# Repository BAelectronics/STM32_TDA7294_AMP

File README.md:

# Kapcsolódó videók / Related videos
[Part 1 (showing)](https://youtu.be/A-13wsFyjP8)
The language of the video is Hungarian, but English subtitles are available.

[Part 2 (HW & SW részletek)](https://youtu.be/WkM5X-X5rjU)

# STM32 vezérelt TDA7294 erősítő
A videóban bemutatott és a projekthez tartozó fájlok, rajzok, kódok stb.

A vezérlőpanel kapcsolása és nyákterve KiCad 5.1 programmal készült.
Az erősítőpanel és a táppanel Sprint Layout 5.0 programmal készült.
Az erősítőpanel kapcsolási rajza nem saját tervezés, ez képként megtalálható.

# STM32 Controlled TDA7294 Amplifier
Files, schematics, codes, etc. Everything what presented in the video and associated with the project.

The control board schematic and PCB designed with KiCad 5.1.
The amplifier board and power supply board designed with Sprint Layout 5.0.
The schematic of the amplifier board is not my own design, it can be found as picture.

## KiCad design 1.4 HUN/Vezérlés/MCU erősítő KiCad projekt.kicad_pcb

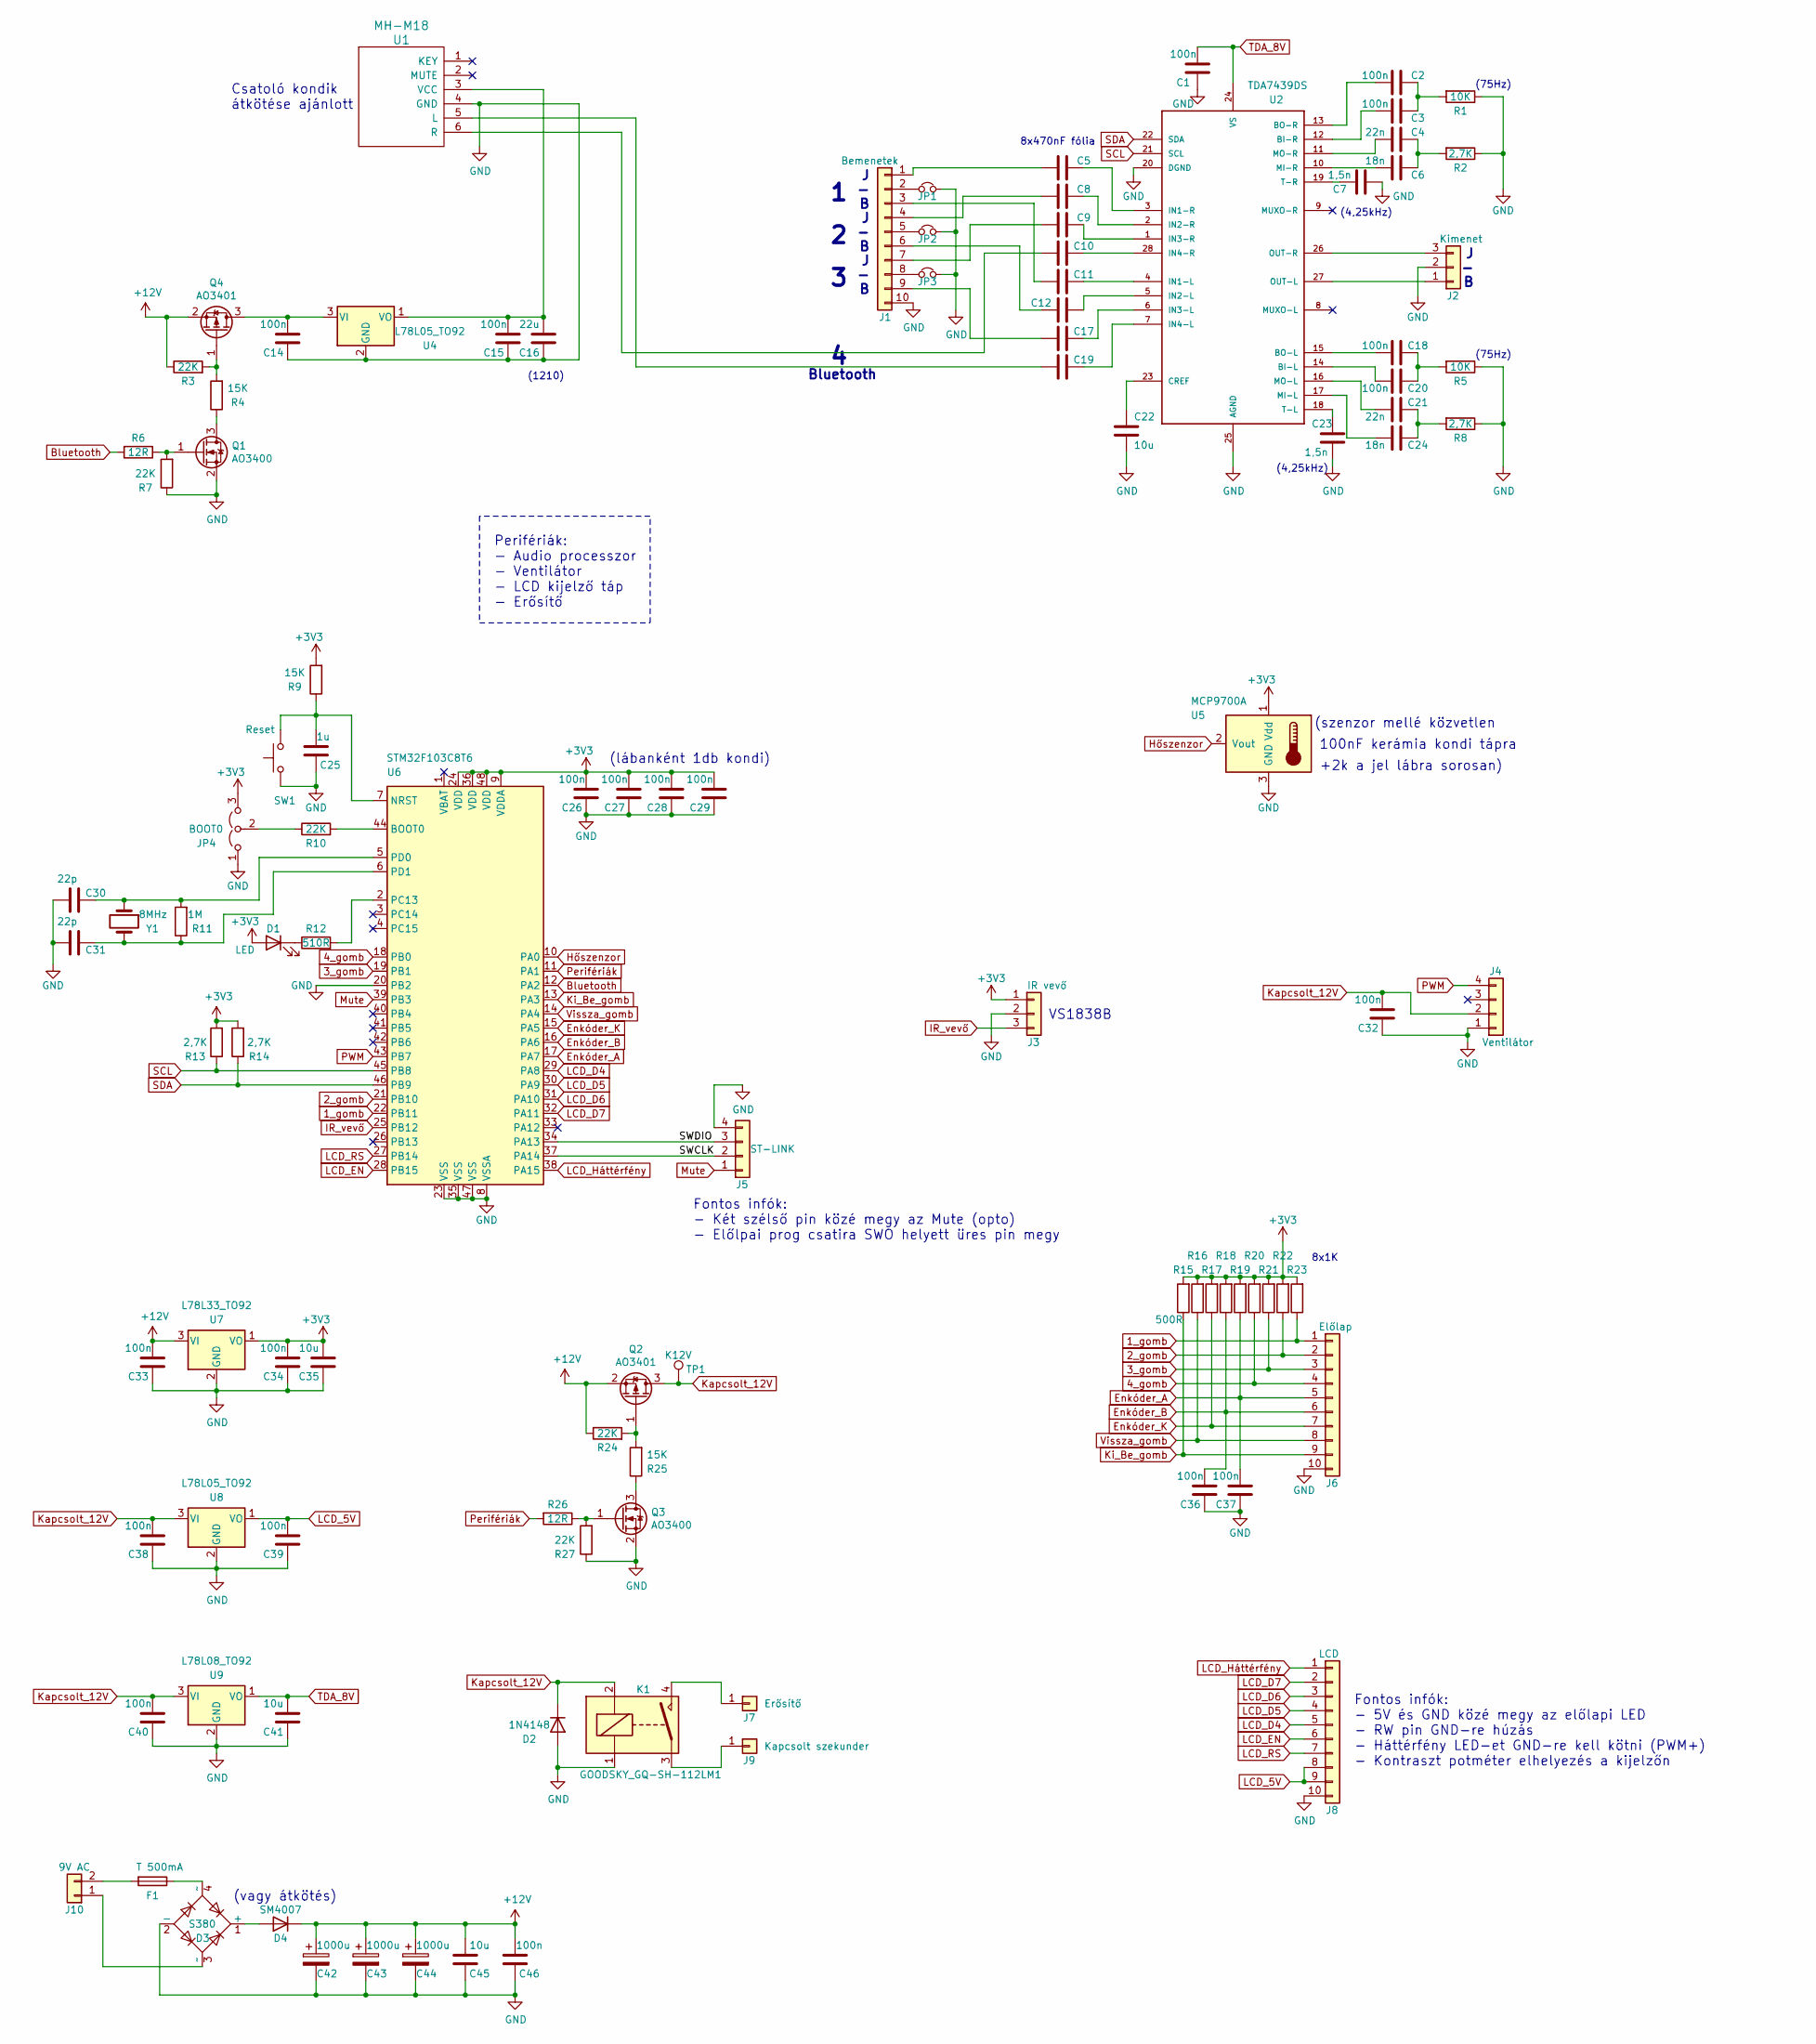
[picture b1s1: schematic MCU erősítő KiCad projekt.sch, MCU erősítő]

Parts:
C1, C14, C15, C26, C27, C28, C29, C32, C33, C34, C36, C37, C38, C39, C40, C46: 100n; C_0805_2012Metric
C2, C3, C18, C20: 100n; C_Rect_L7.0mm_W2.5mm_P5.00mm
C4, C21: 22n; C_Rect_L7.0mm_W2.5mm_P5.00mm
C5, C8, C9, C10, C11, C12, C17, C19: 470n; C_Rect_L7.2mm_W3.5mm_P5.00mm_FKS2_FKP2_MKS2_MKP2
C6, C24: 18n; C_Rect_L7.0mm_W2.5mm_P5.00mm
C7, C23: 1,5n; C_Rect_L7.0mm_W2.5mm_P5.00mm
C16: 22u; C_1210_3225Metric
C22, C35, C41, C45: 10u; C_1206_3216Metric
C25: 1u; C_0805_2012Metric
C30, C31: 22p; C_0805_2012Metric
C42, C43, C44: 1000u; CP_Radial_D8.0mm_P3.50mm
D1: LED; LED_0805_2012Metric
D2: 1N4148; D_DO-35_SOD27_P7.62mm_Horizontal
D3: S380; Diode_Bridge_TO-269AA
D4: SM4007; D_MELF
F1: T 500mA; Fuse_Littelfuse_372_D8.50mm
J1: Bemenetek; JST_PH_B10B-PH-K_1x10_P2.00mm_Vertical
J2: Kimenet; JST_PH_B3B-PH-K_1x03_P2.00mm_Vertical
J3: IR vevő; JST_PH_B3B-PH-K_1x03_P2.00mm_Vertical
J4: Ventilátor; Molex_KK-254_AE-6410-04A_1x04_P2.54mm_Vertical
J5: ST-LINK; JST_PH_B4B-PH-K_1x04_P2.00mm_Vertical
J6: Előlap; JST_PH_B10B-PH-K_1x10_P2.00mm_Vertical
J7: Erősítő; SolderWirePad_1x02_P5.08mm_Drill1.5mm_saru
J8: LCD; JST_PH_B10B-PH-K_1x10_P2.00mm_Vertical
J9: Kapcsolt szekunder; SolderWirePad_1x02_P5.08mm_Drill1.5mm_saru
J10: 9V AC; TerminalBlock_RND_205-00012_1x02_P5.00mm_Horizontal
JP1: Jumper_1_GND; SolderJumper-2_P1.3mm_Open_Pad1.0x1.5mm
JP2: Jumper_2_GND; SolderJumper-2_P1.3mm_Open_Pad1.0x1.5mm
JP3: Jumper_3_GND; SolderJumper-2_P1.3mm_Open_Pad1.0x1.5mm
JP4: BOOT0; PinHeader_1x03_P2.54mm_Vertical
K1: GOODSKY_GQ-SH-112LM1
Q1, Q3: AO3400; SOT-23
Q2, Q4: AO3401; SOT-23
R1, R5: 10K; R_0805_2012Metric
R2, R8, R13, R14: 2,7K; R_0805_2012Metric
R3, R7, R10, R24, R27: 22K; R_0805_2012Metric
R4, R9: 15K; R_0805_2012Metric
R6, R26: 12R; R_0805_2012Metric
R11: 1M; R_0805_2012Metric
R12: 510R; R_0805_2012Metric
R15: 500R; R_0805_2012Metric
R16, R17, R18, R19, R20, R21, R22, R23: 1K; R_0805_2012Metric
R25: 15K; R_1206_3216Metric
SW1: Reset; SW_SPST_FSMSM
TP1: K12V; TestPoint_Pad_D1.0mm
U1: MH-M18; MH-M18_Bluetooth_Audio
U2: TDA7439DS; SOIC-28W_7.5x17.9mm_P1.27mm
U4, U8: L78L05_TO92; TO-92_Inline_mod
U5: MCP9700A; JST_PH_B3B-PH-K_1x03_P2.00mm_Vertical
U6: STM32F103C8T6; LQFP-48_7x7mm_P0.5mm
U7: L78L33_TO92; TO-92_Inline_mod
U9: L78L08_TO92; TO-92_Inline_mod
Y1: 8MHz; Crystal_HC49-U_Vertical

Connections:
1_gomb: J6.1, R23.1, U6.22 (PB11)
2_gomb: J6.2, R22.1, U6.21 (PB10)
3_gomb: J6.3, R21.1, U6.19 (PB1)
4_gomb: J6.4, R20.1, U6.18 (PB0)
+3V3: C26.2, C27.2, C28.2, C29.2, C34.2, C35.2, D1.2 (A), J3.1, JP4.3 (B), R9.2, R13.2, R14.2, R15.2, R16.2, R17.2, R18.2, R19.2, R20.2, R21.2, R22.2, R23.2, U5.1 (Vdd), U6.9 (VDDA), U6.24 (VDD), U6.36 (VDD), U6.48 (VDD), U7.1 (VO)
+12V: C33.2, C42.1, C43.1, C44.1, C45.2, C46.2, D4.1 (K), Q2.2 (S), Q4.2 (S), R3.1, R24.1, U7.3 (VI)
/SWCLK: J5.2, U6.37 (PA14)
/SWDIO: J5.3, U6.34 (PA13)
Bluetooth: R6.2, U6.12 (PA2)
Enkóder_A: C37.2, J6.5, R19.1, U6.17 (PA7)
Enkóder_B: C36.2, J6.6, R18.1, U6.16 (PA6)
Enkóder_K: J6.7, R17.1, U6.15 (PA5)
GND: C1.1, C7.2, C14.1, C15.1, C16.1, C22.1, C23.1, C25.1, C26.1, C27.1, C28.1, C29.1, C30.1, C31.1, C32.1, C33.1, C34.1, C35.1, C36.1, C37.1, C38.1, C39.1, C40.1, C41.1, C42.2, C43.2, C44.2, C45.1, C46.1, D2.2 (A), D3.2 (-), J1.10, J2.2, J3.2, J4.1, J5.4, J6.10, J8.10, JP1.2, JP2.2, JP3.2, JP4.1 (A), K1.1, Q1.2 (S), Q3.2 (S), R1.1, R2.1, R5.1, R7.1, R8.1, R27.1, SW1.1, U1.4 (GND), U2.20 (DGND), U2.25 (AGND), U4.2 (GND), U5.3 (GND), U6.8 (VSSA), U6.20 (PB2), U6.23 (VSS), U6.35 (VSS), U6.47 (VSS), U7.2 (GND), U8.2 (GND), U9.2 (GND)
Hőszenzor: U5.2 (Vout), U6.10 (PA0)
IR_vevő: J3.3, U6.25 (PB12)
Kapcsolt_12V: C32.2, C38.2, C40.2, D2.1 (K), J4.2, K1.2, Q2.3 (D), TP1.1, U8.3 (VI), U9.3 (VI)
Ki_Be_gomb: J6.9, R15.1, U6.13 (PA3)
LCD_5V: C39.2, J8.8, J8.9, U8.1 (VO)
LCD_D4: J8.5, U6.29 (PA8)
LCD_D5: J8.4, U6.30 (PA9)
LCD_D6: J8.3, U6.31 (PA10)
LCD_D7: J8.2, U6.32 (PA11)
LCD_EN: J8.6, U6.28 (PB15)
LCD_Háttérfény: J8.1, U6.38 (PA15)
LCD_RS: J8.7, U6.27 (PB14)
Mute: J5.1, U6.39 (PB3)
unnamed: C2.1, C3.1, R1.2
unnamed: C2.2, U2.13 (BO-R)
unnamed: C3.2, U2.12 (BI-R)
unnamed: C4.1, C6.1, R2.2
unnamed: C4.2, U2.11 (MO-R)
unnamed: C5.1, U2.3 (IN1-R)
unnamed: C5.2, J1.1
unnamed: C6.2, U2.10 (MI-R)
unnamed: C7.1, U2.19 (T-R)
unnamed: C8.1, U2.2 (IN2-R)
unnamed: C8.2, J1.4
unnamed: C9.1, U2.1 (IN3-R)
unnamed: C9.2, J1.7
unnamed: C10.1, U2.28 (IN4-R)
unnamed: C10.2, U1.6 (R)
unnamed: C11.1, U2.4 (IN1-L)
unnamed: C11.2, J1.3
unnamed: C12.1, U2.5 (IN2-L)
unnamed: C12.2, J1.6
unnamed: C14.2, Q4.3 (D), U4.3 (VI)
unnamed: C15.2, C16.2, U1.3 (VCC), U4.1 (VO)
unnamed: C17.1, U2.6 (IN3-L)
unnamed: C17.2, J1.9
unnamed: C18.1, C20.1, R5.2
unnamed: C18.2, U2.15 (BO-L)
unnamed: C19.1, U2.7 (IN4-L)
unnamed: C19.2, U1.5 (L)
unnamed: C20.2, U2.14 (BI-L)
unnamed: C21.1, C24.1, R8.2
unnamed: C21.2, U2.16 (MO-L)
unnamed: C22.2, U2.23 (CREF)
unnamed: C23.2, U2.18 (T-L)
unnamed: C24.2, U2.17 (MI-L)
unnamed: C25.2, R9.1, SW1.2, U6.7 (NRST)
unnamed: C30.2, R11.2, U6.5 (PD0), Y1.1
unnamed: C31.2, R11.1, U6.6 (PD1), Y1.2
unnamed: D1.1 (K), R12.1
unnamed: D3.1 (+), D4.2 (A)
unnamed: D3.3 (~~), J10.1
unnamed: D3.4 (~~), F1.1
unnamed: F1.2, J10.2
unnamed: J1.2, JP1.1
unnamed: J1.5, JP2.1
unnamed: J1.8, JP3.1
unnamed: J2.1, U2.27 (OUT-L)
unnamed: J2.3, U2.26 (OUT-R)
unnamed: J7.1, K1.4
unnamed: J9.1, K1.3
unnamed: JP4.2 (C), R10.1
unnamed: Q1.1 (G), R6.1, R7.2
unnamed: Q1.3 (D), R4.1
unnamed: Q2.1 (G), R24.2, R25.2
unnamed: Q3.1 (G), R26.1, R27.2
unnamed: Q3.3 (D), R25.1
unnamed: Q4.1 (G), R3.2, R4.2
unnamed: R10.2, U6.44 (BOOT0)
unnamed: R12.2, U6.2 (PC13)
PWM: J4.4, U6.43 (PB7)
Perifériák: R26.2, U6.11 (PA1)
SCL: R13.1, U2.21 (SCL), U6.45 (PB8)
SDA: R14.1, U2.22 (SDA), U6.46 (PB9)
TDA_8V: C1.2, C41.2, U2.24 (VS), U9.1 (VO)
Vissza_gomb: J6.8, R16.1, U6.14 (PA4)

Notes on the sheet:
8x470nF fólia
(vagy átkötés)
(lábanként 1db kondi)
(szenzor mellé közvetlen
100nF kerámia kondi tápra
8x1K
Perifériák: - Audio processzor - Ventilátor - LCD kijelző táp - Erősítő
+2k a jel lábra sorosan)
(1210)
Fontos infók: - 5V és GND közé megy az előlapi LED - RW pin GND-re húzás - Háttérfény LED-et GND-re kell kötni (PWM+) - Kontraszt potméter elhelyezés a kijelzőn
Bluetooth
Csatoló kondik átkötése ajánlott
(75Hz)
(4,25kHz)
Fontos infók: - Két szélső pin közé megy az Mute (opto) - Előlpai prog csatira SWO helyett üres pin megy
VS1838B

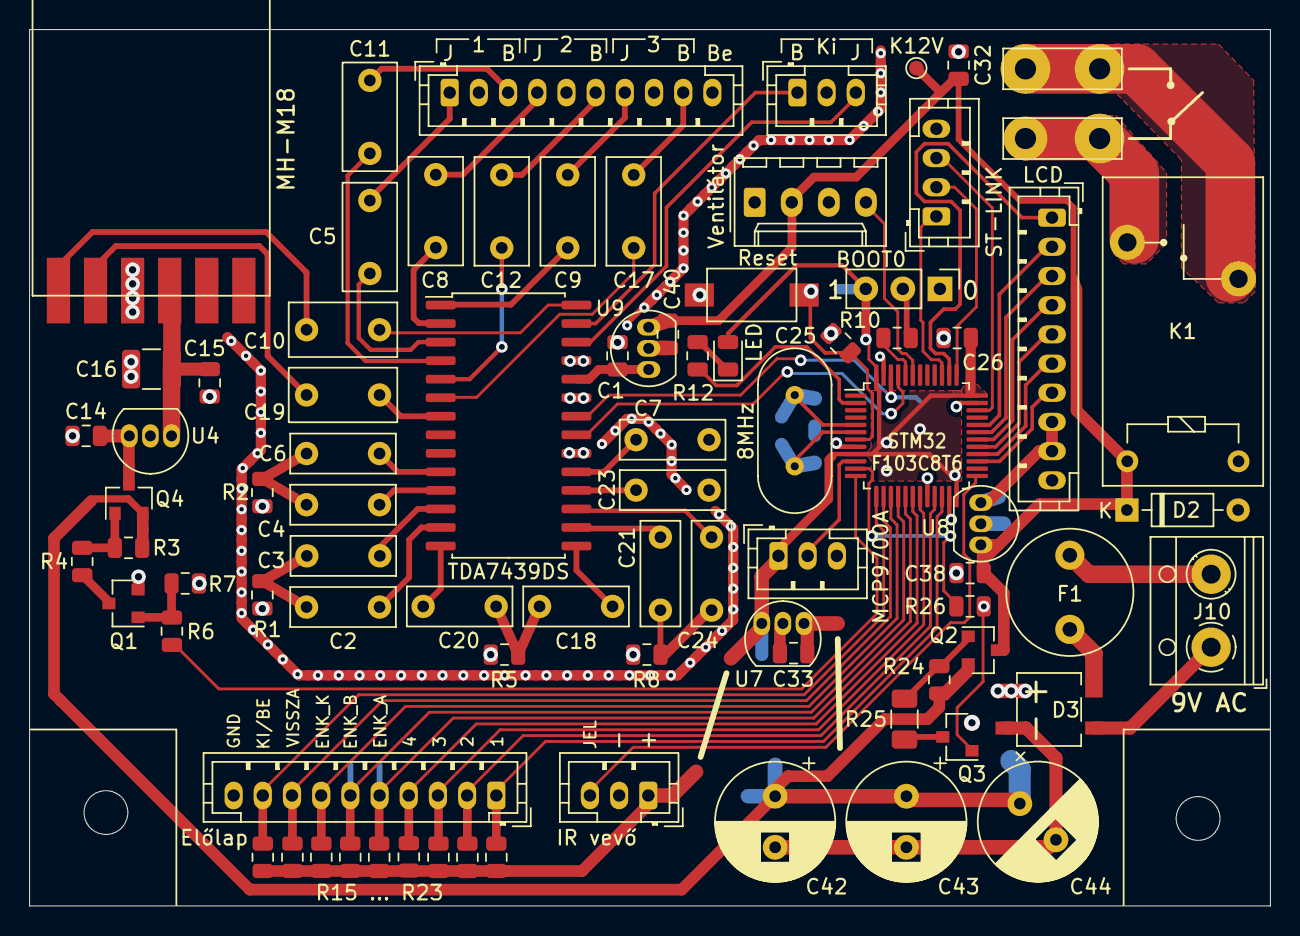
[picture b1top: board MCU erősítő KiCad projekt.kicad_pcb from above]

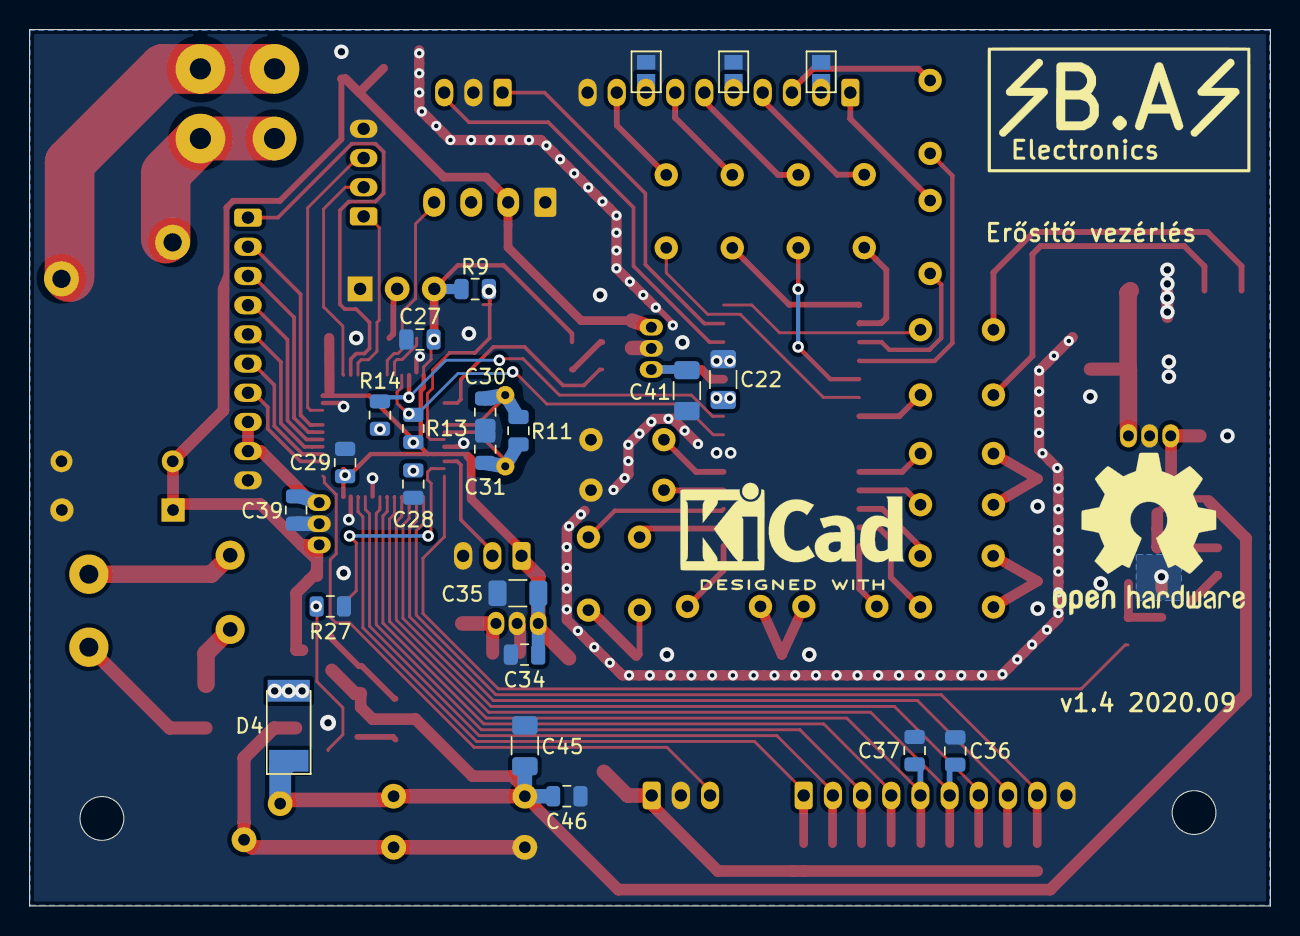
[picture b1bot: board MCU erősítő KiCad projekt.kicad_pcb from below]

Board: 2 copper layers, 85.0 x 60.0 mm, 107 parts (23 on the bottom side), 89 nets.
